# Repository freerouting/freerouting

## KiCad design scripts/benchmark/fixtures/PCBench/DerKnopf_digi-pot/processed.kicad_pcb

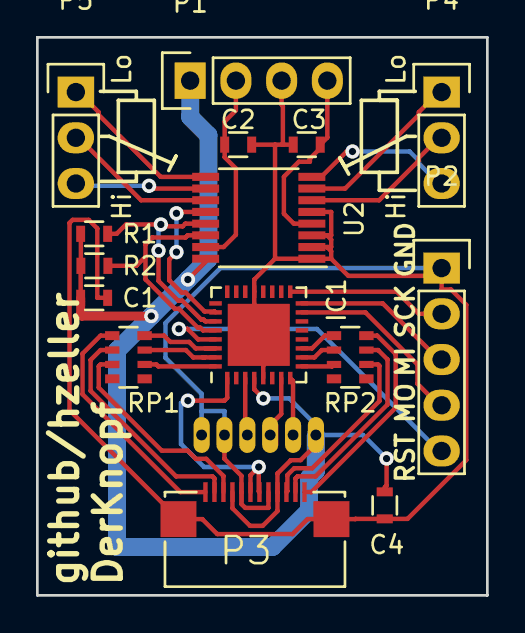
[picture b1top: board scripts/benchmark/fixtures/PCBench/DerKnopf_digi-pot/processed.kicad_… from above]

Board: 2 copper layers, 25.0 x 31.0 mm, 16 parts (1 on the bottom side), 33 nets.

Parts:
C1, C2, C3, C4: 100n; R_0603
IC1: ATTINY48-M; QFN-32-1EP_5x5mm_Pitch0.5mm
P1: CONN_01X04; Pin_Header_Straight_1x04
P2: CONN_01X05; Pin_Header_Straight_1x05
P3: CONN_01X13; FlatFlexConn
P4, P5: CONN_01X03; Pin_Header_Straight_1x03
R1, R2: 4k7; R_0603
RP1, RP2: R_PACK4; R_Array_Convex_4x0603
U1: CUI-C14
U2: DS1882; TSSOP-16_4.4x5mm_Pitch0.65mm

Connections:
+5V: C1.1, C4.1, IC1.4, P1.1, P3.4, P3.9, R1.1, R2.1, U1.6, U2.16
/A: P3.1, RP1.1
/B: P3.2, RP1.2
/Button: IC1.3, U1.3
/C: P3.3, RP1.3
/CE: IC1.26, U2.12
/D: P3.10, RP2.2
/E: P3.11, RP2.3
/F: P3.12, RP2.4
/IR-signal: IC1.1, P3.6, P3.7
/MISO: IC1.16, P2.3
/MOSI: IC1.15, P2.4
/Pot0_H: P4.3, U2.8
/Pot0_L: P4.1, U2.7
/Pot0_W: P4.2, U2.6
/Pot1_H: P5.3, U2.10
/Pot1_L: P5.1, U2.9
/Pot1_W: P5.2, U2.11
/QuadA: IC1.7, U1.4
/QuadB: IC1.8, U1.5
/RESET: IC1.29, P2.5
/SCK: IC1.17, P2.2
/SCL: IC1.28, R2.2, U2.14
/SDA: IC1.27, R1.2, U2.13
GND: C1.2, C2.2, C3.2, C4.2, IC1.5, IC1.21, P1.3, P2.1, P3.5, P3.8, P3.13, U1.1, U1.2, U2.1, U2.2, U2.3, U2.5
unnamed: IC1.9, RP2.7
unnamed: IC1.10, RP2.6
unnamed: IC1.11, RP2.5
unnamed: IC1.30, RP1.8
unnamed: IC1.31, RP1.7
unnamed: IC1.32, RP1.6
V+: C2.1, P1.2, U2.15
V-: C3.1, P1.4, U2.4

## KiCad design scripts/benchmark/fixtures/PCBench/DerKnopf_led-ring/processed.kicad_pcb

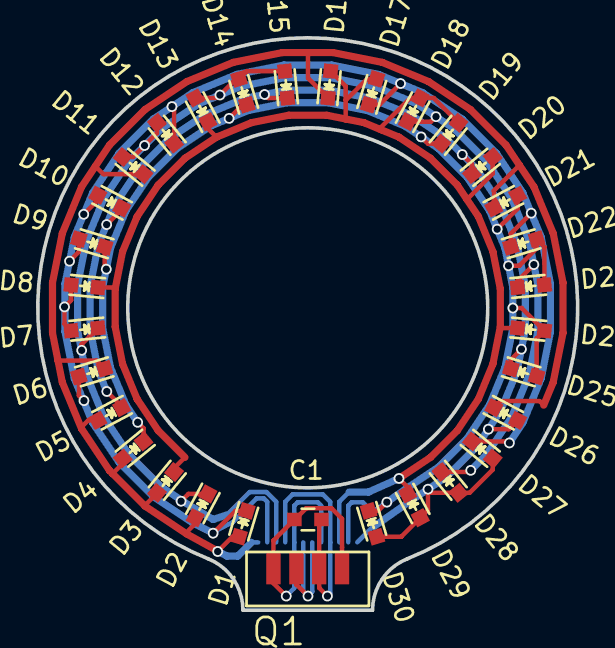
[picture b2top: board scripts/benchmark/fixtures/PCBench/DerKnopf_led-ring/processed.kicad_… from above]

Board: 2 copper layers, 30.0 x 31.8 mm, 33 parts (1 on the bottom side), 9 nets.

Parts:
C1: 100n; C_0603
D1, D2, D3, D4, D5, D6, D7, D8, D9, D10, D11, D12, D13, D14, D15, D16, D17, D18, D19, D20, D21, D22, D23, D24, D25, D26, D27, D28, D29, D30: LED; LED_0603
P1: CONN_01X12; FlatFlex
Q1: TSOP75338; TSOP75xx

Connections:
/GND: C1.2, P1.5, P1.8, Q1.1, Q1.4
/IR-signal: P1.6, P1.7, Q1.3
/VCC: C1.1, P1.4, P1.9, Q1.2
A: D1.2, D2.2, D3.2, D4.2, D5.2, D6.1, D11.1, D16.1, D21.1, D26.1, P1.1
B: D1.1, D6.2, D7.2, D8.2, D9.2, D10.2, D12.1, D17.1, D22.1, D27.1, P1.2
C: D2.1, D7.1, D11.2, D12.2, D13.2, D14.2, D15.2, D18.1, D23.1, D28.1, P1.3
D: D3.1, D8.1, D13.1, D16.2, D17.2, D18.2, D19.2, D20.2, D24.1, D29.1, P1.10
E: D4.1, D9.1, D14.1, D19.1, D21.2, D22.2, D23.2, D24.2, D25.2, D30.1, P1.11
F: D5.1, D10.1, D15.1, D20.1, D25.1, D26.2, D27.2, D28.2, D29.2, D30.2, P1.12

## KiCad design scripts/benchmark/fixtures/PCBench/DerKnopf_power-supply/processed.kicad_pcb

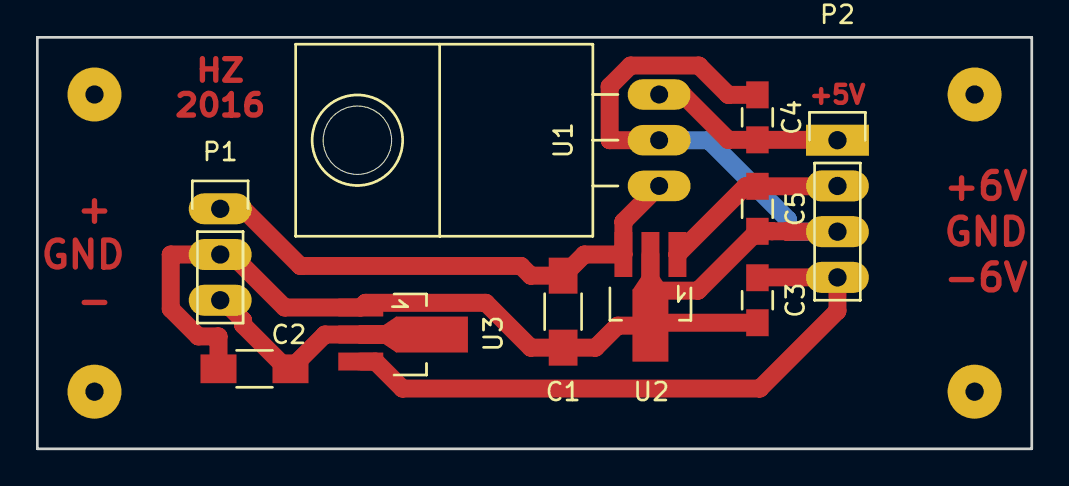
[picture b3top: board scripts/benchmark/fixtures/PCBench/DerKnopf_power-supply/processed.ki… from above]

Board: 2 copper layers, 55.2 x 22.9 mm, 14 parts (0 on the bottom side), 6 nets.

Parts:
C1, C2: 10u; C_1206_HandSoldering
C3, C4, C5: 100n; C_0805_HandSoldering
P1: CONN_01X03; Pin_Header_Straight_1x03
P2: CONN_01X04; Pin_Header_Straight_1x04
R: D; Pin_Header_Straight_1x01
R_2, R_3, R_4: D; Pin_Header_Straight_1x01
U1: 7805; TO-220_Neutral123_Horizontal_LargePads
U2: 78L06; SOT89-3_Housing_Handsoldering
U3: 79L06; SOT89-3_Housing_Handsoldering

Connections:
/+5V: C4.1, P2.1, U1.3
/+6V: C5.1, P2.2, U2.1
/+15V: C1.1, P1.1, U1.1, U2.3
/-6V: C3.1, P2.4, U3.3
/-15V: C2.1, P1.3, U3.2
GND: C1.2, C2.2, C3.2, C4.2, C5.2, P1.2, P2.3, U1.2, U2.2, U3.1
